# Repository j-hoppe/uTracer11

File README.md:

# uTracer11

„uTracer11“ (read: "micro-program-tracer for PDP-11") is a signal probe that is plugged into older UNIBUS PDP-11s.

The CPU state is visualized on a host PC via a graphical user interface (GUI)

It is primarily used for micro-stepping the CPU, as a function demo, repair tool, or for entertainment.

See: https://www.retrocmp.com/tools/utracer11

## Directory structure:
* common - C++ sources needed for M93X2 Arduino and GUI ... message protocol
* CSerialPort - C++ sources for RS232 interface Linux/Windows
* duktape - embedded JScript engine

* gui - main user interface, WxWidgets project Linux/Windows

* KM11.pcb - KiCad project for KM11 adapter probe

* M93X2probe.pcb - KiCad project for M93X2 probe PCB

* M93X2probe.pio - M93X2 probe Arduino firmware, PlatformI

* M93X2probe.pdp11data - PDP-11 code to be embedded into M93X2 BOOT logic

* Pdp11BusCycleDisas - source branch of UNIBUS traffic disassmebler for different PDP-11 CPUs

* pdp1134sim - case study for a micro machine based simulator, example is a 11/34 simple program loop

* resources - helper data files, scanned jpegs

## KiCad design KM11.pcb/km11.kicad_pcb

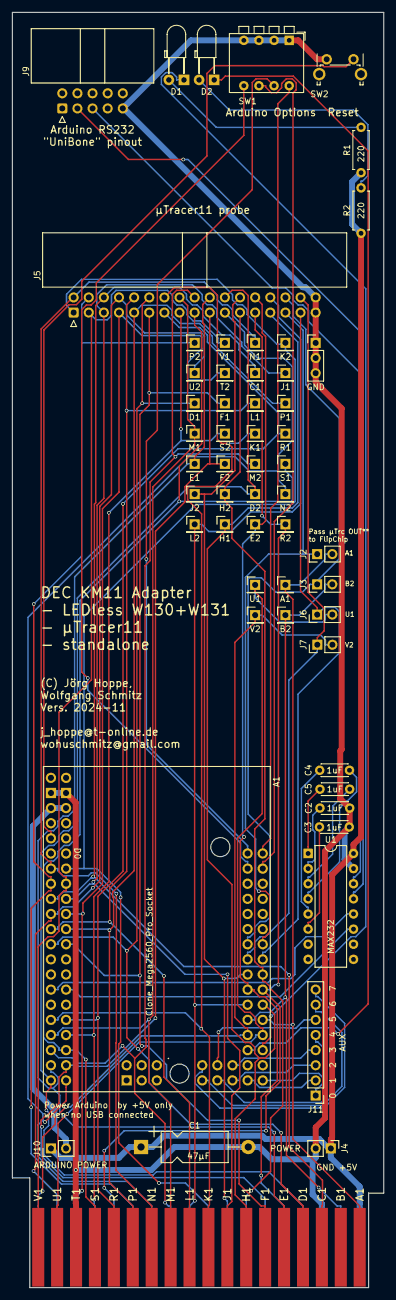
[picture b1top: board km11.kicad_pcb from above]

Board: 2 copper layers, 62.4 x 214.1 mm, 56 parts (0 on the bottom side), 66 nets.

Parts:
A1: Clone_Mega2560_Pro_Socket
C1: 47µF; CP_Axial_L11.0mm_D5.0mm_P18.00mm_Horizontal
C2, C3, C4, C5: 1uF; C_Disc_D4.3mm_W1.9mm_P5.00mm
D1: LED1; LED_D3.0mm_Horizontal_O3.81mm_Z2.0mm
D2: LED2; LED_D3.0mm_Horizontal_O3.81mm_Z2.0mm
J1: PDP11 FlipChipSlot2x18; dec-conn-single-ht-pins-only
J2: PASS_A1; PinHeader_1x02_P2.54mm_Vertical
J3: PASS_B2; PinHeader_1x02_P2.54mm_Vertical
J4: POWER; PinHeader_1x02_P2.54mm_Vertical
J5: µTracer11 2x17 IDC; IDC-Header_2x17_P2.54mm_Horizontal
J6: PASS_U1; PinHeader_1x02_P2.54mm_Vertical
J7: PASS_V2; PinHeader_1x02_P2.54mm_Vertical
J8: GND; PinHeader_1x03_P2.54mm_Vertical
J9: UART1_RS232_Schneid-Klemm_2x5; IDC-Header_2x05_P2.54mm_Horizontal
J10: ARDUINO POWER; PinHeader_1x02_P2.54mm_Vertical
J11: AUX; PinHeader_1x08_P2.54mm_Vertical
R1, R2: 220; R_Axial_DIN0207_L6.3mm_D2.5mm_P7.62mm_Horizontal
SW1: Option; SW_DIP_SPSTx04_Piano_CTS_Series194-4MSTN_W7.62mm_P2.54mm
SW2: Reset; SW_Tactile_SPST_Angled_PTS645Vx58-2LFS
TP1: R2; PinHeader_1x01_P2.54mm_Vertical
TP2: N2; PinHeader_1x01_P2.54mm_Vertical
TP3: S1; PinHeader_1x01_P2.54mm_Vertical
TP4: R1; PinHeader_1x01_P2.54mm_Vertical
TP5: P1; PinHeader_1x01_P2.54mm_Vertical
TP6: J1; PinHeader_1x01_P2.54mm_Vertical
TP7: K2; PinHeader_1x01_P2.54mm_Vertical
TP8: E2; PinHeader_1x01_P2.54mm_Vertical
TP9: D2; PinHeader_1x01_P2.54mm_Vertical
TP10: M2; PinHeader_1x01_P2.54mm_Vertical
TP11: K1; PinHeader_1x01_P2.54mm_Vertical
TP12: L1; PinHeader_1x01_P2.54mm_Vertical
TP13: C1; PinHeader_1x01_P2.54mm_Vertical
TP14: N1; PinHeader_1x01_P2.54mm_Vertical
TP15: H1; PinHeader_1x01_P2.54mm_Vertical
TP16: H2; PinHeader_1x01_P2.54mm_Vertical
TP17: F2; PinHeader_1x01_P2.54mm_Vertical
TP18: S2; PinHeader_1x01_P2.54mm_Vertical
TP19: F1; PinHeader_1x01_P2.54mm_Vertical
TP20: T2; PinHeader_1x01_P2.54mm_Vertical
TP21: V1; PinHeader_1x01_P2.54mm_Vertical
TP22: L2; PinHeader_1x01_P2.54mm_Vertical
TP23: J2; PinHeader_1x01_P2.54mm_Vertical
TP24: E1; PinHeader_1x01_P2.54mm_Vertical
TP25: M1; PinHeader_1x01_P2.54mm_Vertical
TP26: D1; PinHeader_1x01_P2.54mm_Vertical
TP27: U2; PinHeader_1x01_P2.54mm_Vertical
TP28: P2; PinHeader_1x01_P2.54mm_Vertical
TP29: A1; PinHeader_1x01_P2.54mm_Vertical
TP30: B2; PinHeader_1x01_P2.54mm_Vertical
TP31: U1; PinHeader_1x01_P2.54mm_Vertical
TP32: V2; PinHeader_1x01_P2.54mm_Vertical
U1: MAX232; DIP-16_W7.62mm

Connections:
5V: C1.1, J1.A2, J4.1, J10.1, R1.1, R2.1, U1.16 (VCC)
/arduino/ARDUINO_5V: A1.5V1 (5V), A1.5V3 (5V), J10.2
/arduino/AUX0: A1.D46, J11.1
/arduino/AUX1: A1.D47, J11.2
/arduino/AUX2: A1.D48, J11.3
/arduino/AUX3: A1.D49, J11.4
/arduino/AUX4: A1.D50 (D50_MISO), J11.5
/arduino/AUX5: A1.D51 (D51_MOSI), J11.6
/arduino/AUX6: A1.D52 (D52_SCK), J11.7
/arduino/AUX7: A1.D53 (D53_CS), J11.8
/arduino/LED1: A1.D42, D1.1 (K)
/arduino/LED2: A1.D43, D2.1 (K)
/arduino/RS232-RX: A1.D19 (D19/RX1), U1.12 (R1OUT)
/arduino/RS232-TX: A1.D18 (D18/TX1), U1.11 (T1IN)
C1: A1.D7, J1.C1, J5.6, TP13.1
D1: A1.D13, J1.D1, J5.12, TP26.1
D2: A1.D31, J1.D2, J5.22, TP9.1
E1: A1.D29, J1.E1, J5.20, TP24.1
E2: A1.D35, J1.E2, J5.26, TP8.1
F1: A1.D12, J1.F1, J5.11, TP19.1
F2: A1.D28, J1.F2, J5.19, TP17.1
GND: A1.GND1 (GND), A1.GND2 (GND), C1.2, C2.2, C3.2, J1.C2, J1.T1, J4.2, J5.33, J5.34, J8.1, J8.2, J8.3, J9.9 (GND), SW1.1, SW1.2, SW1.3, SW1.4, SW2.1, U1.15 (GND)
H1: A1.D36, J1.H1, J5.27, TP15.1
H2: A1.D32, J1.H2, J5.23, TP16.1
J1: A1.D6, J1.J1, J5.5, TP6.1
J2: A1.D33, J1.J2, J5.24, TP23.1
K1: A1.D23, J1.K1, J5.14, TP11.1
K2: A1.D2 (D2_INT0), J1.K2, J5.1, TP7.1
L1: A1.D11, J1.L1, J5.10, TP12.1
L2: A1.D37, J1.L2, J5.28, TP22.1
M1: A1.D25, J1.M1, J5.16, TP25.1
M2: A1.D27, J1.M2, J5.18, TP10.1
N1: A1.D3 (D3_INT1), J1.N1, J5.2, TP14.1
N2: A1.D30, J1.N2, J5.21, TP2.1
unnamed: A1.A0, SW1.8
unnamed: A1.A1, SW1.7
unnamed: A1.A2, SW1.6
unnamed: A1.A3, SW1.5
unnamed: A1.RST1 (RESET), SW2.2
unnamed: D1.2 (A), R1.2
unnamed: D2.2 (A), R2.2
unnamed: J9.3 (RXD), U1.13 (R1IN)
unnamed: J9.5 (TXD), U1.14 (T1OUT)
unnamed: C5.1, U1.1 (C1+)
unnamed: C5.2, U1.3 (C1-)
unnamed: C4.1, U1.4 (C2+)
unnamed: C4.2, U1.5 (C2-)
unnamed: C2.1, U1.2 (VS+)
unnamed: C3.1, U1.6 (VS-)
P1: A1.D10, J1.P1, J5.9, TP5.1
P2: A1.D5, J1.P2, J5.4, TP28.1
PDP_A1_L: A1.D38, J1.A1, J2.2, TP29.1
PDP_B2_L: A1.D39, J1.B2, J3.2, TP30.1
PDP_U1_L: A1.D40, J1.U1, J6.2, TP31.1
PDP_V2_L: A1.D41, J1.V2, J7.2, TP32.1
R1: A1.D22, J1.R1, J5.13, TP4.1
R2: A1.D34, J1.R2, J5.25, TP1.1
S1: A1.D26, J1.S1, J5.17, TP3.1
S2: A1.D24, J1.S2, J5.15, TP18.1
T2: A1.D8, J1.T2, J5.7, TP20.1
TRACER_A1_L: A1.A12, J2.1, J5.29
TRACER_B2_L: A1.A13, J3.1, J5.30
TRACER_U1_L: A1.A14, J5.31, J6.1
TRACER_V2_L: A1.A15, J5.32, J7.1
U2: A1.D9, J1.U2, J5.8, TP27.1
V1: A1.D4, J1.V1, J5.3, TP21.1

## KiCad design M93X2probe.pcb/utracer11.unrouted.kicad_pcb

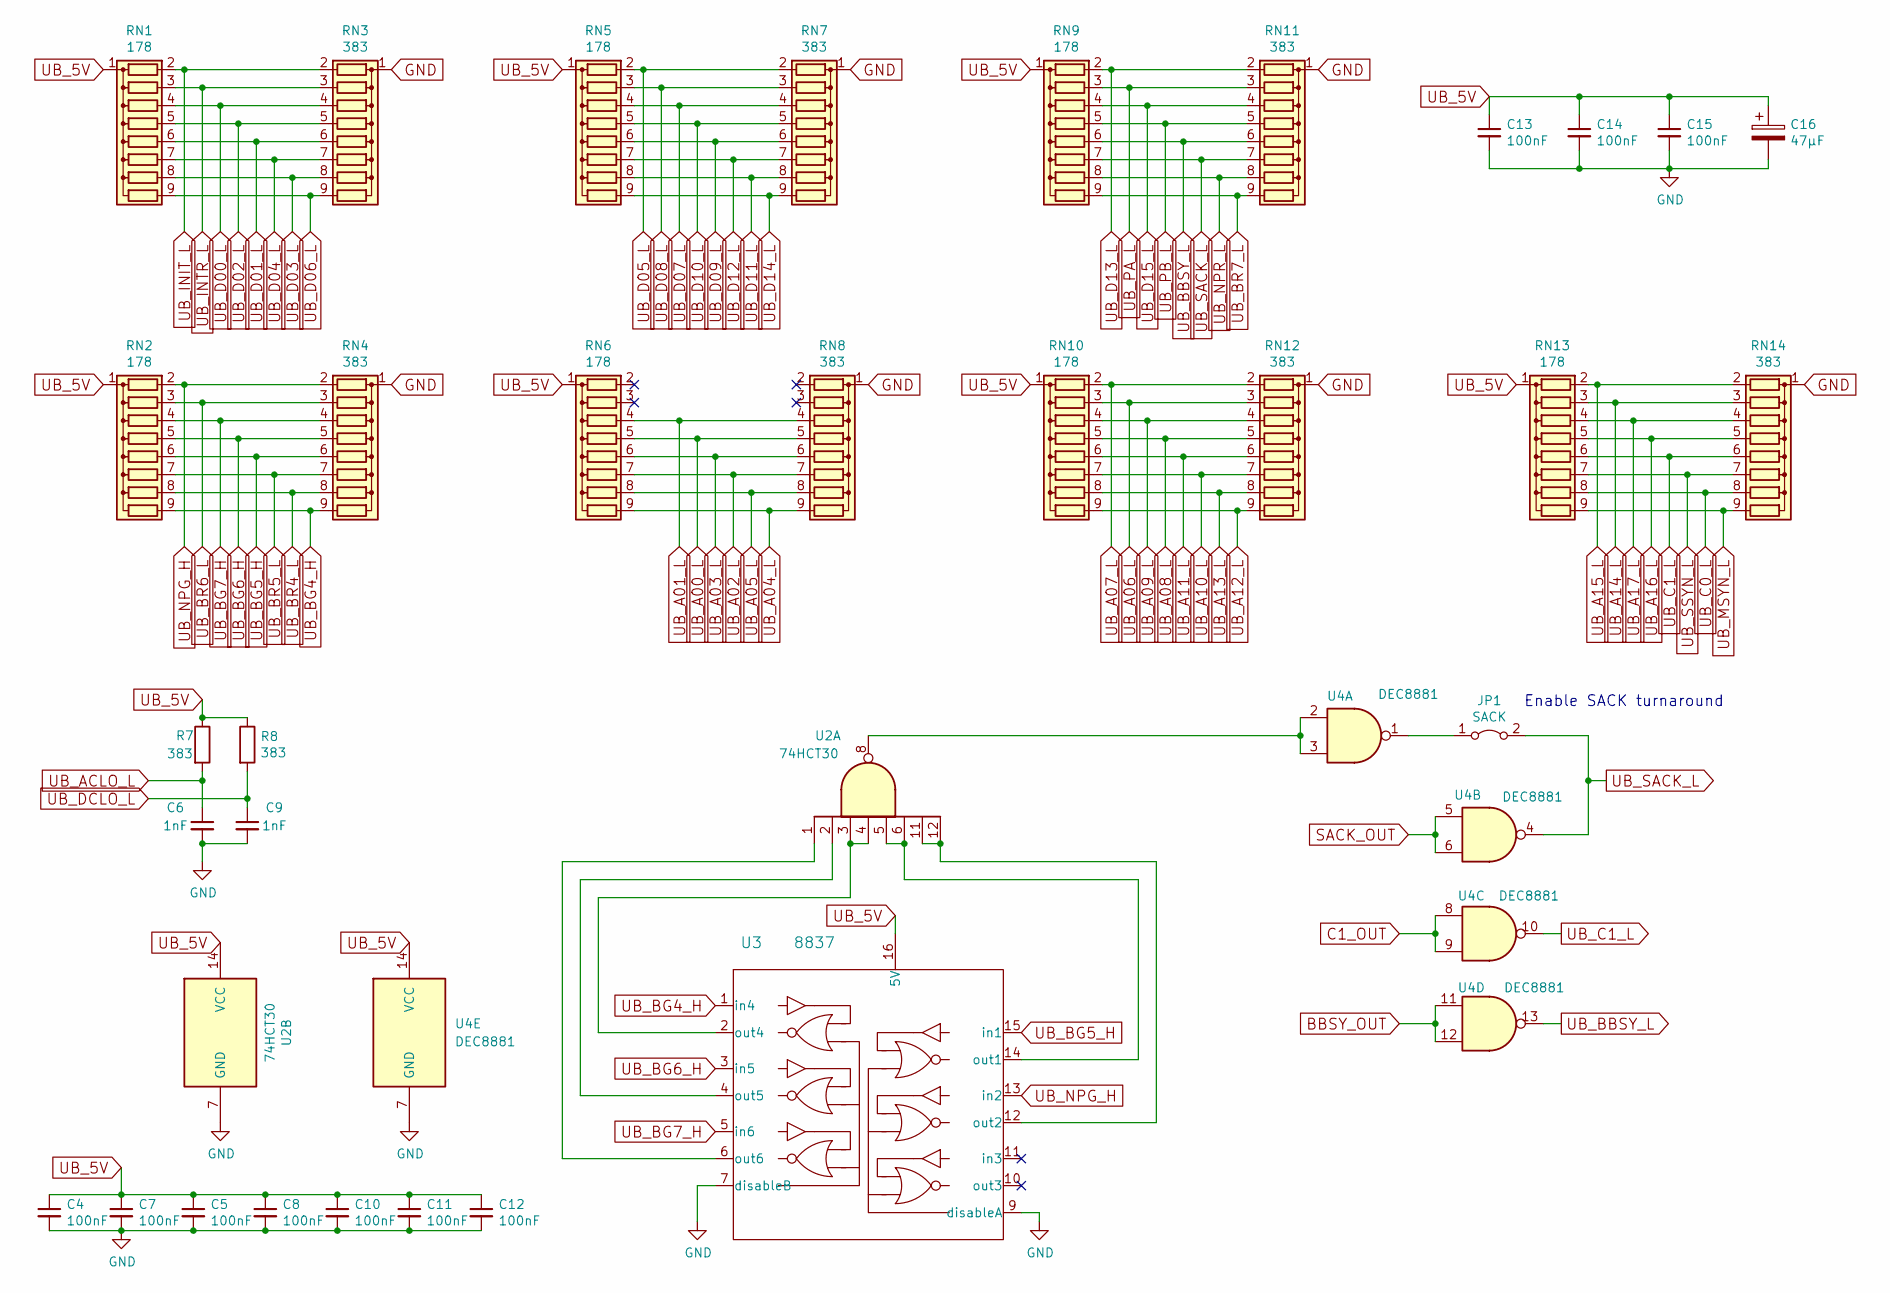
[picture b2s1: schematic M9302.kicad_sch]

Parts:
C4, C5, C7, C8, C10, C11, C12, C13, C14, C15: 100nF; C_Disc_D4.3mm_W1.9mm_P5.00mm; LCSC C49678
C6, C9: 1nF; C_Disc_D4.3mm_W1.9mm_P5.00mm; LCSC C46653
C16: 47µF; CP_Axial_L11.0mm_D5.0mm_P18.00mm_Horizontal
JP1: SACK; PinHeader_1x02_P2.54mm_Vertical
R7, R8: 383; R_Axial_DIN0207_L6.3mm_D2.5mm_P2.54mm_Vertical; LCSC C17655
RN1, RN2, RN5, RN6, RN9, RN10, RN13: 178; R_Array_SIP9
RN3, RN4, RN7, RN8, RN11, RN12, RN14: 383; R_Array_SIP9
U2: 74HCT30; DIP-14_W7.62mm; LCSC C2865549
U3: 8837; DIP-16_W7.62mm
U4: DEC8881; DIP-14_W7.62mm

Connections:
BBSY_OUT: U4.11, U4.12; also elsewhere on the board
C1_OUT: U4.8, U4.9; also elsewhere on the board
GND: C4.2, C5.2, C6.2, C7.2, C8.2, C9.2, C10.2, C11.2, C12.2, C13.2, C14.2, C15.2, C16.2, RN3.1 (common), RN4.1 (common), RN7.1 (common), RN8.1 (common), RN11.1 (common), RN12.1 (common), RN14.1 (common), U2.7 (GND), U3.7 (disableB), U3.8 (GND), U3.9 (disableA), U4.7 (GND); also elsewhere on the board
unnamed: JP1.1 (A), U4.1
unnamed: U2.8, U4.2, U4.3
unnamed: U2.5, U2.6, U3.14 (out1)
unnamed: U2.11, U2.12, U3.12 (out2)
unnamed: U2.3, U2.4, U3.2 (out4)
unnamed: U2.2, U3.4 (out5)
unnamed: U2.1, U3.6 (out6)
SACK_OUT: U4.5, U4.6; also elsewhere on the board
UB_5V: C4.1, C5.1, C7.1, C8.1, C10.1, C11.1, C12.1, C13.1, C14.1, C15.1, C16.1, R7.1, R8.1, RN1.1 (common), RN2.1 (common), RN5.1 (common), RN6.1 (common), RN9.1 (common), RN10.1 (common), RN13.1 (common), U2.14 (VCC), U3.16 (5V), U4.14 (VCC); also elsewhere on the board
UB_A00_L: RN6.5 (R4), RN8.5 (R4); also elsewhere on the board
UB_A01_L: RN6.4 (R3), RN8.4 (R3); also elsewhere on the board
UB_A02_L: RN6.7 (R6), RN8.7 (R6); also elsewhere on the board
UB_A03_L: RN6.6 (R5), RN8.6 (R5); also elsewhere on the board
UB_A04_L: RN6.9 (R8), RN8.9 (R8); also elsewhere on the board
UB_A05_L: RN6.8 (R7), RN8.8 (R7); also elsewhere on the board
UB_A06_L: RN10.3 (R2), RN12.3 (R2); also elsewhere on the board
UB_A07_L: RN10.2 (R1), RN12.2 (R1); also elsewhere on the board
UB_A08_L: RN10.5 (R4), RN12.5 (R4); also elsewhere on the board
UB_A09_L: RN10.4 (R3), RN12.4 (R3); also elsewhere on the board
UB_A10_L: RN10.7 (R6), RN12.7 (R6); also elsewhere on the board
UB_A11_L: RN10.6 (R5), RN12.6 (R5); also elsewhere on the board
UB_A12_L: RN10.9 (R8), RN12.9 (R8); also elsewhere on the board
UB_A13_L: RN10.8 (R7), RN12.8 (R7); also elsewhere on the board
UB_A14_L: RN13.3 (R2), RN14.3 (R2); also elsewhere on the board
UB_A15_L: RN13.2 (R1), RN14.2 (R1); also elsewhere on the board
UB_A16_L: RN13.5 (R4), RN14.5 (R4); also elsewhere on the board
UB_A17_L: RN13.4 (R3), RN14.4 (R3); also elsewhere on the board
UB_ACLO_L: C6.1, R7.2; also elsewhere on the board
UB_BBSY_L: RN9.6 (R5), RN11.6 (R5), U4.13; also elsewhere on the board
UB_BG4_H: RN2.9 (R8), RN4.9 (R8), U3.1 (in4); also elsewhere on the board
UB_BG5_H: RN2.6 (R5), RN4.6 (R5), U3.15 (in1); also elsewhere on the board
UB_BG6_H: RN2.5 (R4), RN4.5 (R4), U3.3 (in5); also elsewhere on the board
UB_BG7_H: RN2.4 (R3), RN4.4 (R3), U3.5 (in6); also elsewhere on the board
UB_BR4_L: RN2.8 (R7), RN4.8 (R7); also elsewhere on the board
UB_BR5_L: RN2.7 (R6), RN4.7 (R6); also elsewhere on the board
UB_BR6_L: RN2.3 (R2), RN4.3 (R2); also elsewhere on the board
UB_BR7_L: RN9.9 (R8), RN11.9 (R8); also elsewhere on the board
UB_C0_L: RN13.8 (R7), RN14.8 (R7); also elsewhere on the board
UB_C1_L: RN13.6 (R5), RN14.6 (R5), U4.10; also elsewhere on the board
UB_D00_L: RN1.4 (R3), RN3.4 (R3); also elsewhere on the board
UB_D01_L: RN1.6 (R5), RN3.6 (R5); also elsewhere on the board
UB_D02_L: RN1.5 (R4), RN3.5 (R4); also elsewhere on the board
UB_D03_L: RN1.8 (R7), RN3.8 (R7); also elsewhere on the board
UB_D04_L: RN1.7 (R6), RN3.7 (R6); also elsewhere on the board
UB_D05_L: RN5.2 (R1), RN7.2 (R1); also elsewhere on the board
UB_D06_L: RN1.9 (R8), RN3.9 (R8); also elsewhere on the board
UB_D07_L: RN5.4 (R3), RN7.4 (R3); also elsewhere on the board
UB_D08_L: RN5.3 (R2), RN7.3 (R2); also elsewhere on the board
UB_D09_L: RN5.6 (R5), RN7.6 (R5); also elsewhere on the board
UB_D10_L: RN5.5 (R4), RN7.5 (R4); also elsewhere on the board
UB_D11_L: RN5.8 (R7), RN7.8 (R7); also elsewhere on the board
UB_D12_L: RN5.7 (R6), RN7.7 (R6); also elsewhere on the board
UB_D13_L: RN9.2 (R1), RN11.2 (R1); also elsewhere on the board
UB_D14_L: RN5.9 (R8), RN7.9 (R8); also elsewhere on the board
UB_D15_L: RN9.4 (R3), RN11.4 (R3); also elsewhere on the board
UB_DCLO_L: C9.1, R8.2; also elsewhere on the board
UB_INIT_L: RN1.2 (R1), RN3.2 (R1); also elsewhere on the board
UB_INTR_L: RN1.3 (R2), RN3.3 (R2); also elsewhere on the board
UB_MSYN_L: RN13.9 (R8), RN14.9 (R8); also elsewhere on the board
UB_NPG_H: RN2.2 (R1), RN4.2 (R1), U3.13 (in2); also elsewhere on the board
UB_NPR_L: RN9.8 (R7), RN11.8 (R7); also elsewhere on the board
UB_PA_L: RN9.3 (R2), RN11.3 (R2); also elsewhere on the board
UB_PB_L: RN9.5 (R4), RN11.5 (R4); also elsewhere on the board
UB_SACK_L: JP1.2 (B), RN9.7 (R6), RN11.7 (R6), U4.4; also elsewhere on the board
UB_SSYN_L: RN13.7 (R6), RN14.7 (R6); also elsewhere on the board

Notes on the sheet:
Enable SACK turnaround

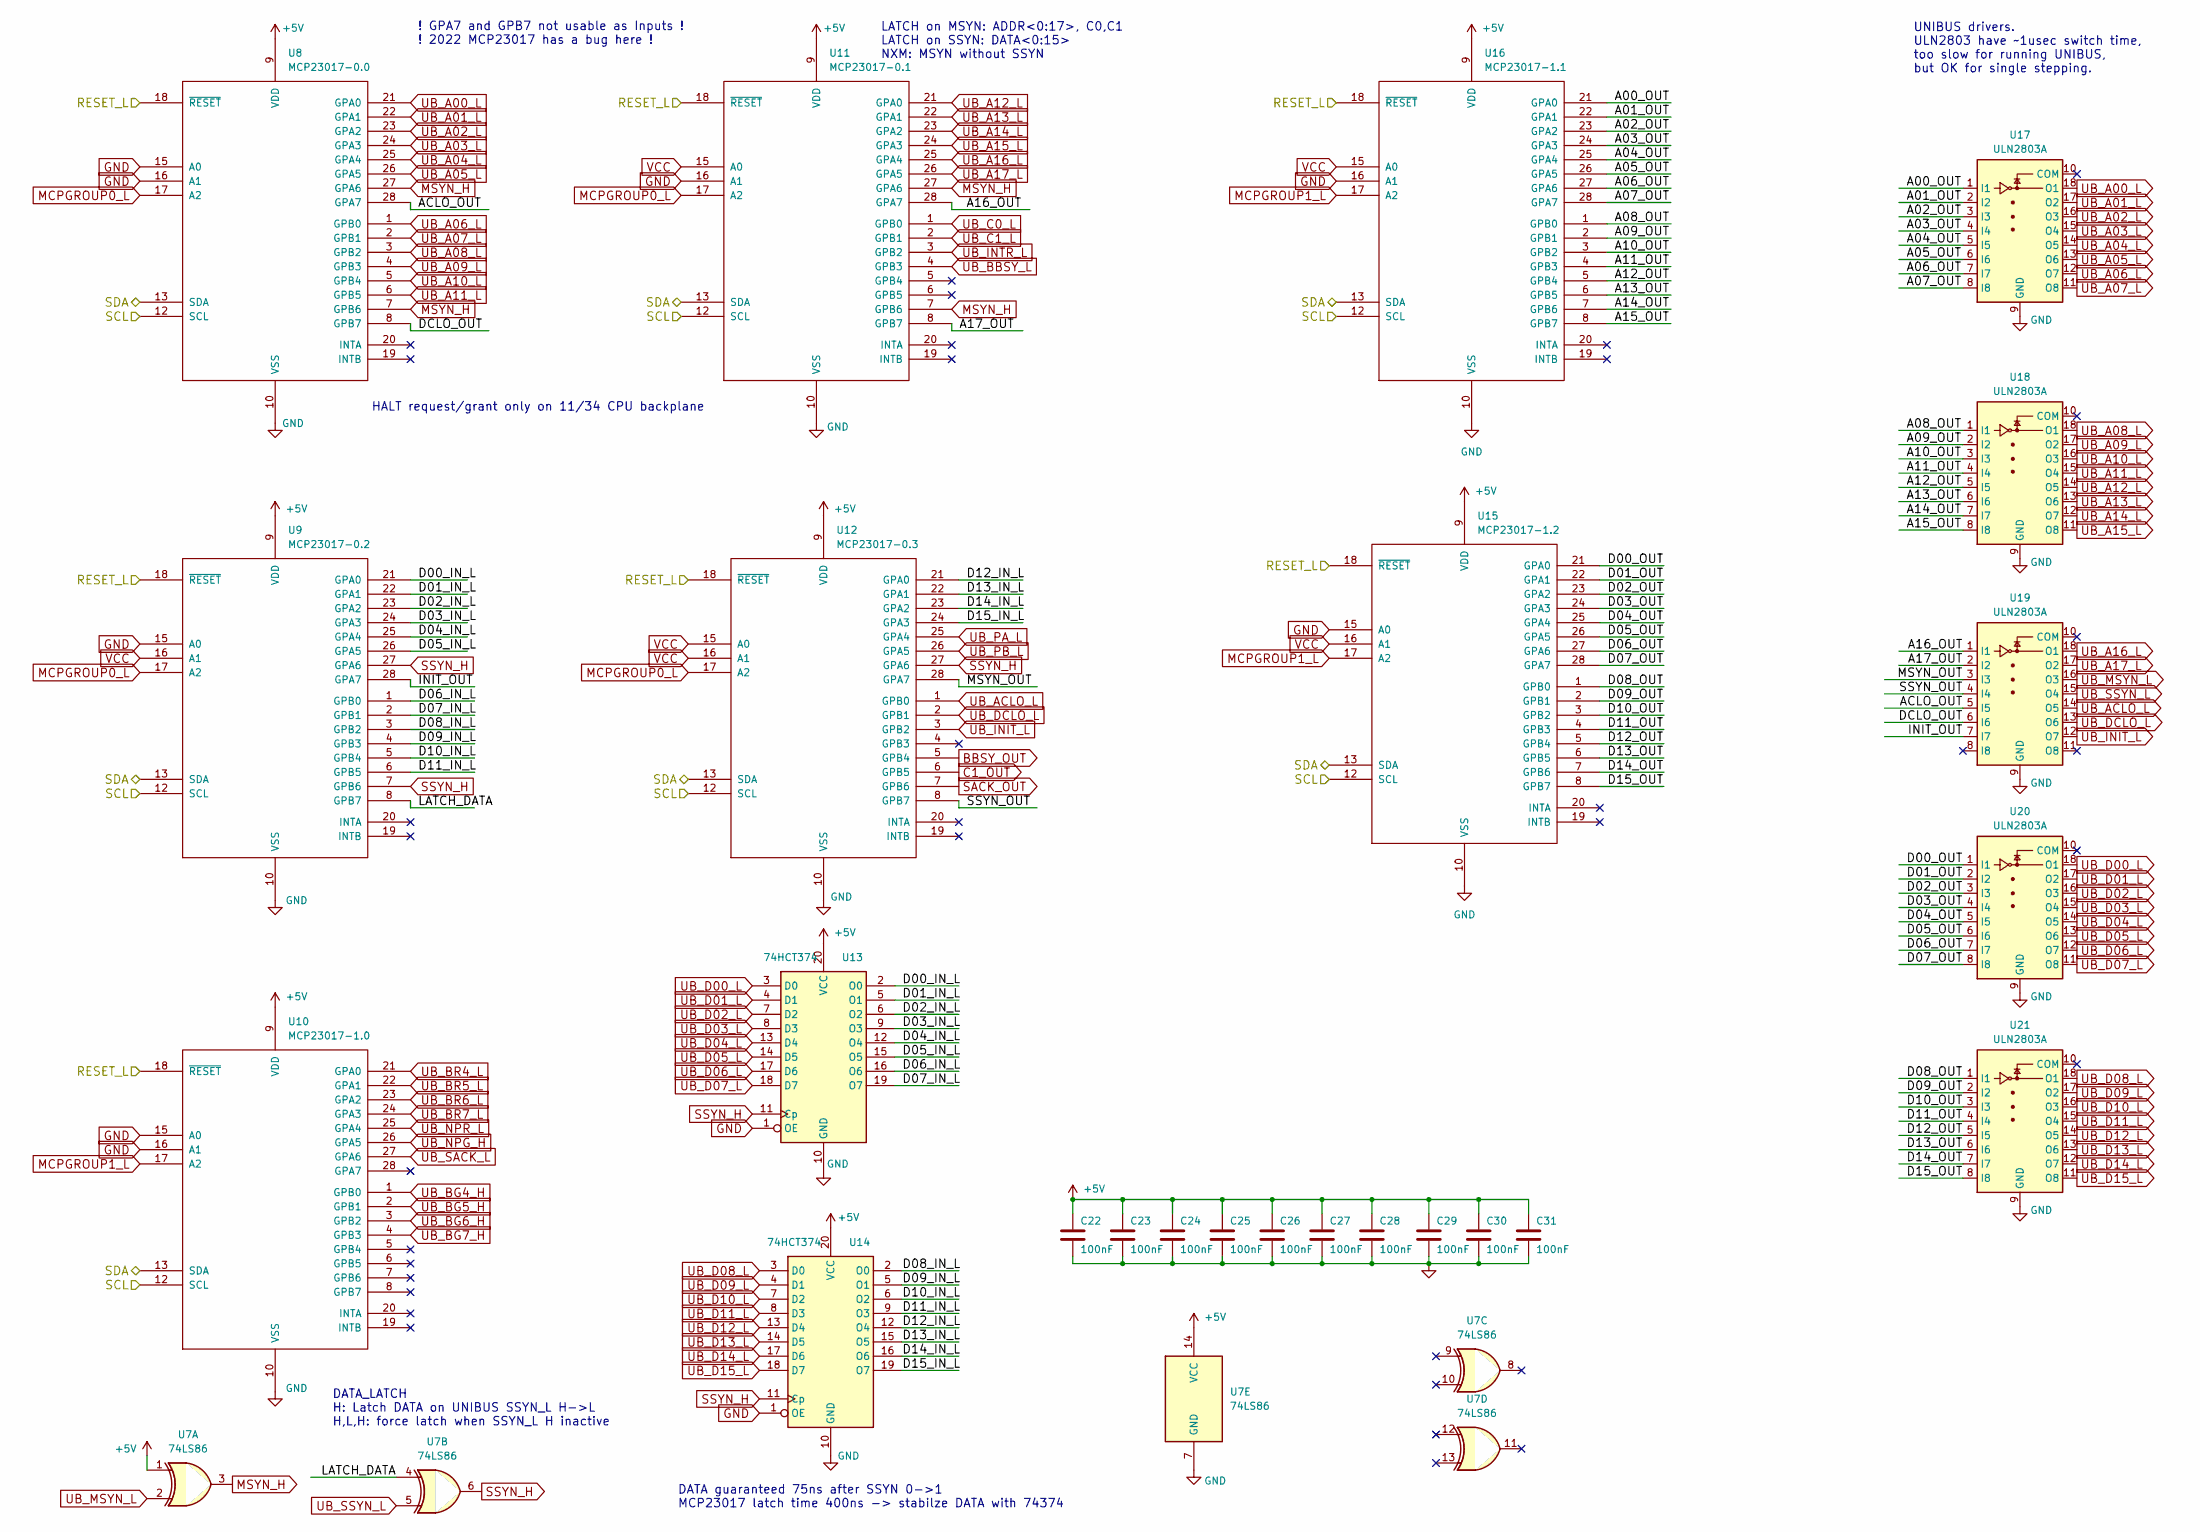
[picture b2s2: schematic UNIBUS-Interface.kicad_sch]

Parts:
C22, C23, C24, C25, C26, C27, C28, C29, C30, C31: 100nF; C_Disc_D4.3mm_W1.9mm_P5.00mm
U7: 74LS86; DIP-14_W7.62mm
U8: MCP23017-0.0; DIP-28_W7.62mm
U9: MCP23017-0.2; DIP-28_W7.62mm
U10: MCP23017-1.0; DIP-28_W7.62mm
U11: MCP23017-0.1; DIP-28_W7.62mm
U12: MCP23017-0.3; DIP-28_W7.62mm
U13, U14: 74HCT374; DIP-20_W7.62mm
U15: MCP23017-1.2; DIP-28_W7.62mm
U16: MCP23017-1.1; DIP-28_W7.62mm
U17, U18, U19, U20, U21: ULN2803A; DIP-18_W7.62mm

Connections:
/MCP_RESET_L: U8.18 (~RESET), U9.18 (~RESET), U10.18 (~RESET), U11.18 (~RESET), U12.18 (~RESET), U15.18 (~RESET), U16.18 (~RESET); also elsewhere on the board
/SCL: U8.12 (SCL), U9.12 (SCL), U10.12 (SCL), U11.12 (SCL), U12.12 (SCL), U15.12 (SCL), U16.12 (SCL); also elsewhere on the board
/SDA: U8.13 (SDA), U9.13 (SDA), U10.13 (SDA), U11.13 (SDA), U12.13 (SDA), U15.13 (SDA), U16.13 (SDA); also elsewhere on the board
/UNIBUS-Interface/A00_OUT: U16.21 (GPA0), U17.1 (I1)
/UNIBUS-Interface/A01_OUT: U16.22 (GPA1), U17.2 (I2)
/UNIBUS-Interface/A02_OUT: U16.23 (GPA2), U17.3 (I3)
/UNIBUS-Interface/A03_OUT: U16.24 (GPA3), U17.4 (I4)
/UNIBUS-Interface/A04_OUT: U16.25 (GPA4), U17.5 (I5)
/UNIBUS-Interface/A05_OUT: U16.26 (GPA5), U17.6 (I6)
/UNIBUS-Interface/A06_OUT: U16.27 (GPA6), U17.7 (I7)
/UNIBUS-Interface/A07_OUT: U16.28 (GPA7), U17.8 (I8)
/UNIBUS-Interface/A08_OUT: U16.1 (GPB0), U18.1 (I1)
/UNIBUS-Interface/A09_OUT: U16.2 (GPB1), U18.2 (I2)
/UNIBUS-Interface/A10_OUT: U16.3 (GPB2), U18.3 (I3)
/UNIBUS-Interface/A11_OUT: U16.4 (GPB3), U18.4 (I4)
/UNIBUS-Interface/A12_OUT: U16.5 (GPB4), U18.5 (I5)
/UNIBUS-Interface/A13_OUT: U16.6 (GPB5), U18.6 (I6)
/UNIBUS-Interface/A14_OUT: U16.7 (GPB6), U18.7 (I7)
/UNIBUS-Interface/A15_OUT: U16.8 (GPB7), U18.8 (I8)
/UNIBUS-Interface/A16_OUT: U11.28 (GPA7), U19.1 (I1)
/UNIBUS-Interface/A17_OUT: U11.8 (GPB7), U19.2 (I2)
/UNIBUS-Interface/ACLO_OUT: U8.28 (GPA7), U19.5 (I5)
/UNIBUS-Interface/D00_IN_L: U9.21 (GPA0), U13.2 (O0)
/UNIBUS-Interface/D00_OUT: U15.21 (GPA0), U20.1 (I1)
/UNIBUS-Interface/D01_IN_L: U9.22 (GPA1), U13.5 (O1)
/UNIBUS-Interface/D01_OUT: U15.22 (GPA1), U20.2 (I2)
/UNIBUS-Interface/D02_IN_L: U9.23 (GPA2), U13.6 (O2)
/UNIBUS-Interface/D02_OUT: U15.23 (GPA2), U20.3 (I3)
/UNIBUS-Interface/D03_IN_L: U9.24 (GPA3), U13.9 (O3)
/UNIBUS-Interface/D03_OUT: U15.24 (GPA3), U20.4 (I4)
/UNIBUS-Interface/D04_IN_L: U9.25 (GPA4), U13.12 (O4)
/UNIBUS-Interface/D04_OUT: U15.25 (GPA4), U20.5 (I5)
/UNIBUS-Interface/D05_IN_L: U9.26 (GPA5), U13.15 (O5)
/UNIBUS-Interface/D05_OUT: U15.26 (GPA5), U20.6 (I6)
/UNIBUS-Interface/D06_IN_L: U9.1 (GPB0), U13.16 (O6)
/UNIBUS-Interface/D06_OUT: U15.27 (GPA6), U20.7 (I7)
/UNIBUS-Interface/D07_IN_L: U9.2 (GPB1), U13.19 (O7)
/UNIBUS-Interface/D07_OUT: U15.28 (GPA7), U20.8 (I8)
/UNIBUS-Interface/D08_IN_L: U9.3 (GPB2), U14.2 (O0)
/UNIBUS-Interface/D08_OUT: U15.1 (GPB0), U21.1 (I1)
/UNIBUS-Interface/D09_IN_L: U9.4 (GPB3), U14.5 (O1)
/UNIBUS-Interface/D09_OUT: U15.2 (GPB1), U21.2 (I2)
/UNIBUS-Interface/D10_IN_L: U9.5 (GPB4), U14.6 (O2)
/UNIBUS-Interface/D10_OUT: U15.3 (GPB2), U21.3 (I3)
/UNIBUS-Interface/D11_IN_L: U9.6 (GPB5), U14.9 (O3)
/UNIBUS-Interface/D11_OUT: U15.4 (GPB3), U21.4 (I4)
/UNIBUS-Interface/D12_IN_L: U12.21 (GPA0), U14.12 (O4)
/UNIBUS-Interface/D12_OUT: U15.5 (GPB4), U21.5 (I5)
/UNIBUS-Interface/D13_IN_L: U12.22 (GPA1), U14.15 (O5)
/UNIBUS-Interface/D13_OUT: U15.6 (GPB5), U21.6 (I6)
/UNIBUS-Interface/D14_IN_L: U12.23 (GPA2), U14.16 (O6)
/UNIBUS-Interface/D14_OUT: U15.7 (GPB6), U21.7 (I7)
/UNIBUS-Interface/D15_IN_L: U12.24 (GPA3), U14.19 (O7)
/UNIBUS-Interface/D15_OUT: U15.8 (GPB7), U21.8 (I8)
/UNIBUS-Interface/DCLO_OUT: U8.8 (GPB7), U19.6 (I6)
/UNIBUS-Interface/INIT_OUT: U9.28 (GPA7), U19.7 (I7)
/UNIBUS-Interface/LATCH_DATA: U7.4, U9.8 (GPB7)
/UNIBUS-Interface/MSYN_OUT: U12.28 (GPA7), U19.3 (I3)
/UNIBUS-Interface/SSYN_OUT: U12.8 (GPB7), U19.4 (I4)
BBSY_OUT: U12.5 (GPB4); also elsewhere on the board
C1_OUT: U12.6 (GPB5); also elsewhere on the board
GND: C22.2, C23.2, C24.2, C25.2, C26.2, C27.2, C28.2, C29.2, C30.2, C31.2, U7.7 (GND), U8.10 (VSS), U8.15 (A0), U8.16 (A1), U9.10 (VSS), U9.15 (A0), U10.10 (VSS), U10.15 (A0), U10.16 (A1), U11.10 (VSS), U11.16 (A1), U12.10 (VSS), U13.1 (OE), U13.10 (GND), U14.1 (OE), U14.10 (GND), U15.10 (VSS), U15.15 (A0), U16.10 (VSS), U16.16 (A1), U17.9 (GND), U18.9 (GND), U19.9 (GND), U20.9 (GND), U21.9 (GND); also elsewhere on the board
MCPGROUP0_L: U8.17 (A2), U9.17 (A2), U11.17 (A2), U12.17 (A2); also elsewhere on the board
MCPGROUP1_L: U10.17 (A2), U15.17 (A2), U16.17 (A2); also elsewhere on the board
MSYN_H: U7.3, U8.7 (GPB6), U8.27 (GPA6), U11.7 (GPB6), U11.27 (GPA6)
SACK_OUT: U12.7 (GPB6); also elsewhere on the board
SSYN_H: U7.6, U9.7 (GPB6), U9.27 (GPA6), U12.27 (GPA6), U13.11 (Cp), U14.11 (Cp)
UB_5V: C22.1, C23.1, C24.1, C25.1, C26.1, C27.1, C28.1, C29.1, C30.1, C31.1, U7.1, U7.14 (VCC), U8.9 (VDD), U9.9 (VDD), U9.16 (A1), U10.9 (VDD), U11.9 (VDD), U11.15 (A0), U12.9 (VDD), U12.15 (A0), U12.16 (A1), U13.20 (VCC), U14.20 (VCC), U15.9 (VDD), U15.16 (A1), U16.9 (VDD), U16.15 (A0); also elsewhere on the board
UB_A00_L: U8.21 (GPA0), U17.18 (O1); also elsewhere on the board
UB_A01_L: U8.22 (GPA1), U17.17 (O2); also elsewhere on the board
UB_A02_L: U8.23 (GPA2), U17.16 (O3); also elsewhere on the board
UB_A03_L: U8.24 (GPA3), U17.15 (O4); also elsewhere on the board
UB_A04_L: U8.25 (GPA4), U17.14 (O5); also elsewhere on the board
UB_A05_L: U8.26 (GPA5), U17.13 (O6); also elsewhere on the board
UB_A06_L: U8.1 (GPB0), U17.12 (O7); also elsewhere on the board
UB_A07_L: U8.2 (GPB1), U17.11 (O8); also elsewhere on the board
UB_A08_L: U8.3 (GPB2), U18.18 (O1); also elsewhere on the board
UB_A09_L: U8.4 (GPB3), U18.17 (O2); also elsewhere on the board
UB_A10_L: U8.5 (GPB4), U18.16 (O3); also elsewhere on the board
UB_A11_L: U8.6 (GPB5), U18.15 (O4); also elsewhere on the board
UB_A12_L: U11.21 (GPA0), U18.14 (O5); also elsewhere on the board
UB_A13_L: U11.22 (GPA1), U18.13 (O6); also elsewhere on the board
UB_A14_L: U11.23 (GPA2), U18.12 (O7); also elsewhere on the board
UB_A15_L: U11.24 (GPA3), U18.11 (O8); also elsewhere on the board
UB_A16_L: U11.25 (GPA4), U19.18 (O1); also elsewhere on the board
UB_A17_L: U11.26 (GPA5), U19.17 (O2); also elsewhere on the board
UB_ACLO_L: U12.1 (GPB0), U19.14 (O5); also elsewhere on the board
UB_BBSY_L: U11.4 (GPB3); also elsewhere on the board
UB_BG4_H: U10.1 (GPB0); also elsewhere on the board
UB_BG5_H: U10.2 (GPB1); also elsewhere on the board
UB_BG6_H: U10.3 (GPB2); also elsewhere on the board
UB_BG7_H: U10.4 (GPB3); also elsewhere on the board
UB_BR4_L: U10.21 (GPA0); also elsewhere on the board
UB_BR5_L: U10.22 (GPA1); also elsewhere on the board
UB_BR6_L: U10.23 (GPA2); also elsewhere on the board
UB_BR7_L: U10.24 (GPA3); also elsewhere on the board
UB_C0_L: U11.1 (GPB0); also elsewhere on the board
UB_C1_L: U11.2 (GPB1); also elsewhere on the board
UB_D00_L: U13.3 (D0), U20.18 (O1); also elsewhere on the board
UB_D01_L: U13.4 (D1), U20.17 (O2); also elsewhere on the board
UB_D02_L: U13.7 (D2), U20.16 (O3); also elsewhere on the board
UB_D03_L: U13.8 (D3), U20.15 (O4); also elsewhere on the board
UB_D04_L: U13.13 (D4), U20.14 (O5); also elsewhere on the board
UB_D05_L: U13.14 (D5), U20.13 (O6); also elsewhere on the board
UB_D06_L: U13.17 (D6), U20.12 (O7); also elsewhere on the board
UB_D07_L: U13.18 (D7), U20.11 (O8); also elsewhere on the board
UB_D08_L: U14.3 (D0), U21.18 (O1); also elsewhere on the board
UB_D09_L: U14.4 (D1), U21.17 (O2); also elsewhere on the board
UB_D10_L: U14.7 (D2), U21.16 (O3); also elsewhere on the board
UB_D11_L: U14.8 (D3), U21.15 (O4); also elsewhere on the board
UB_D12_L: U14.13 (D4), U21.14 (O5); also elsewhere on the board
UB_D13_L: U14.14 (D5), U21.13 (O6); also elsewhere on the board
UB_D14_L: U14.17 (D6), U21.12 (O7); also elsewhere on the board
UB_D15_L: U14.18 (D7), U21.11 (O8); also elsewhere on the board
UB_DCLO_L: U12.2 (GPB1), U19.13 (O6); also elsewhere on the board
UB_INIT_L: U12.3 (GPB2), U19.12 (O7); also elsewhere on the board
UB_INTR_L: U11.3 (GPB2); also elsewhere on the board
UB_MSYN_L: U7.2, U19.16 (O3); also elsewhere on the board
UB_NPG_H: U10.26 (GPA5); also elsewhere on the board
UB_NPR_L: U10.25 (GPA4); also elsewhere on the board
UB_PA_L: U12.25 (GPA4); also elsewhere on the board
UB_PB_L: U12.26 (GPA5); also elsewhere on the board
UB_SACK_L: U10.27 (GPA6); also elsewhere on the board
UB_SSYN_L: U7.5, U19.15 (O4); also elsewhere on the board

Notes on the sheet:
! GPA7 and GPB7 not usable as Inputs ! ! 2022 MCP23017 has a bug here !
LATCH on MSYN: ADDR<0:17>, C0,C1 LATCH on SSYN: DATA<0:15> NXM: MSYN without SSYN
HALT request/grant only on 11/34 CPU backplane
UNIBUS drivers. ULN2803 have ~1usec switch time, too slow for running UNIBUS, but OK for single stepping.
DATA guaranteed 75ns after SSYN 0->1 MCP23017 latch time 400ns -> stabilze DATA with 74374
DATA_LATCH H: Latch DATA on UNIBUS SSYN_L H->L H,L,H: force latch when SSYN_L H inactive

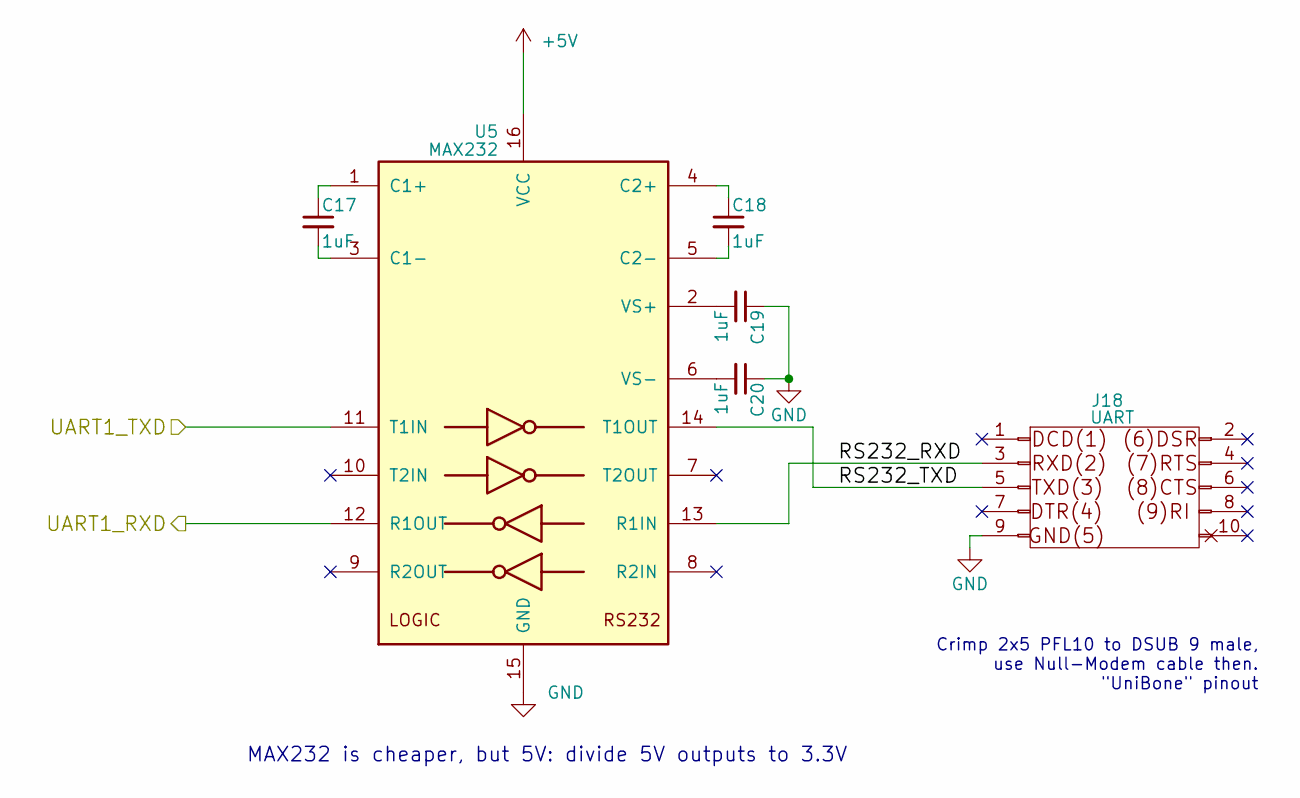
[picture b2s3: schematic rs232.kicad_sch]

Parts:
C17, C19, C20: 1uF; C_Disc_D4.3mm_W1.9mm_P5.00mm; LCSC C28323
C18: 1uF; C_Disc_D4.3mm_W1.9mm_P5.00mm
J18: UART; IDC-Header_2x05_P2.54mm_Horizontal
U5: MAX232; DIP-16_W7.62mm

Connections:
/RS232_RXD: U5.12 (R1OUT); also elsewhere on the board
/RS232_TXD: U5.11 (T1IN); also elsewhere on the board
/rs232/RS232_RXD: J18.3 (RXD), U5.13 (R1IN)
/rs232/RS232_TXD: J18.5 (TXD), U5.14 (T1OUT)
GND: C19.1, C20.1, J18.9 (GND), U5.15 (GND); also elsewhere on the board
unnamed: C17.1, U5.1 (C1+)
unnamed: C17.2, U5.3 (C1-)
unnamed: C18.1, U5.4 (C2+)
unnamed: C18.2, U5.5 (C2-)
unnamed: C19.2, U5.2 (VS+)
unnamed: C20.2, U5.6 (VS-)
UB_5V: U5.16 (VCC); also elsewhere on the board

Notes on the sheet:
MAX232 is cheaper, but 5V: divide 5V outputs to 3.3V
Crimp 2x5 PFL10 to DSUB 9 male, use Null-Modem cable then. "UniBone" pinout

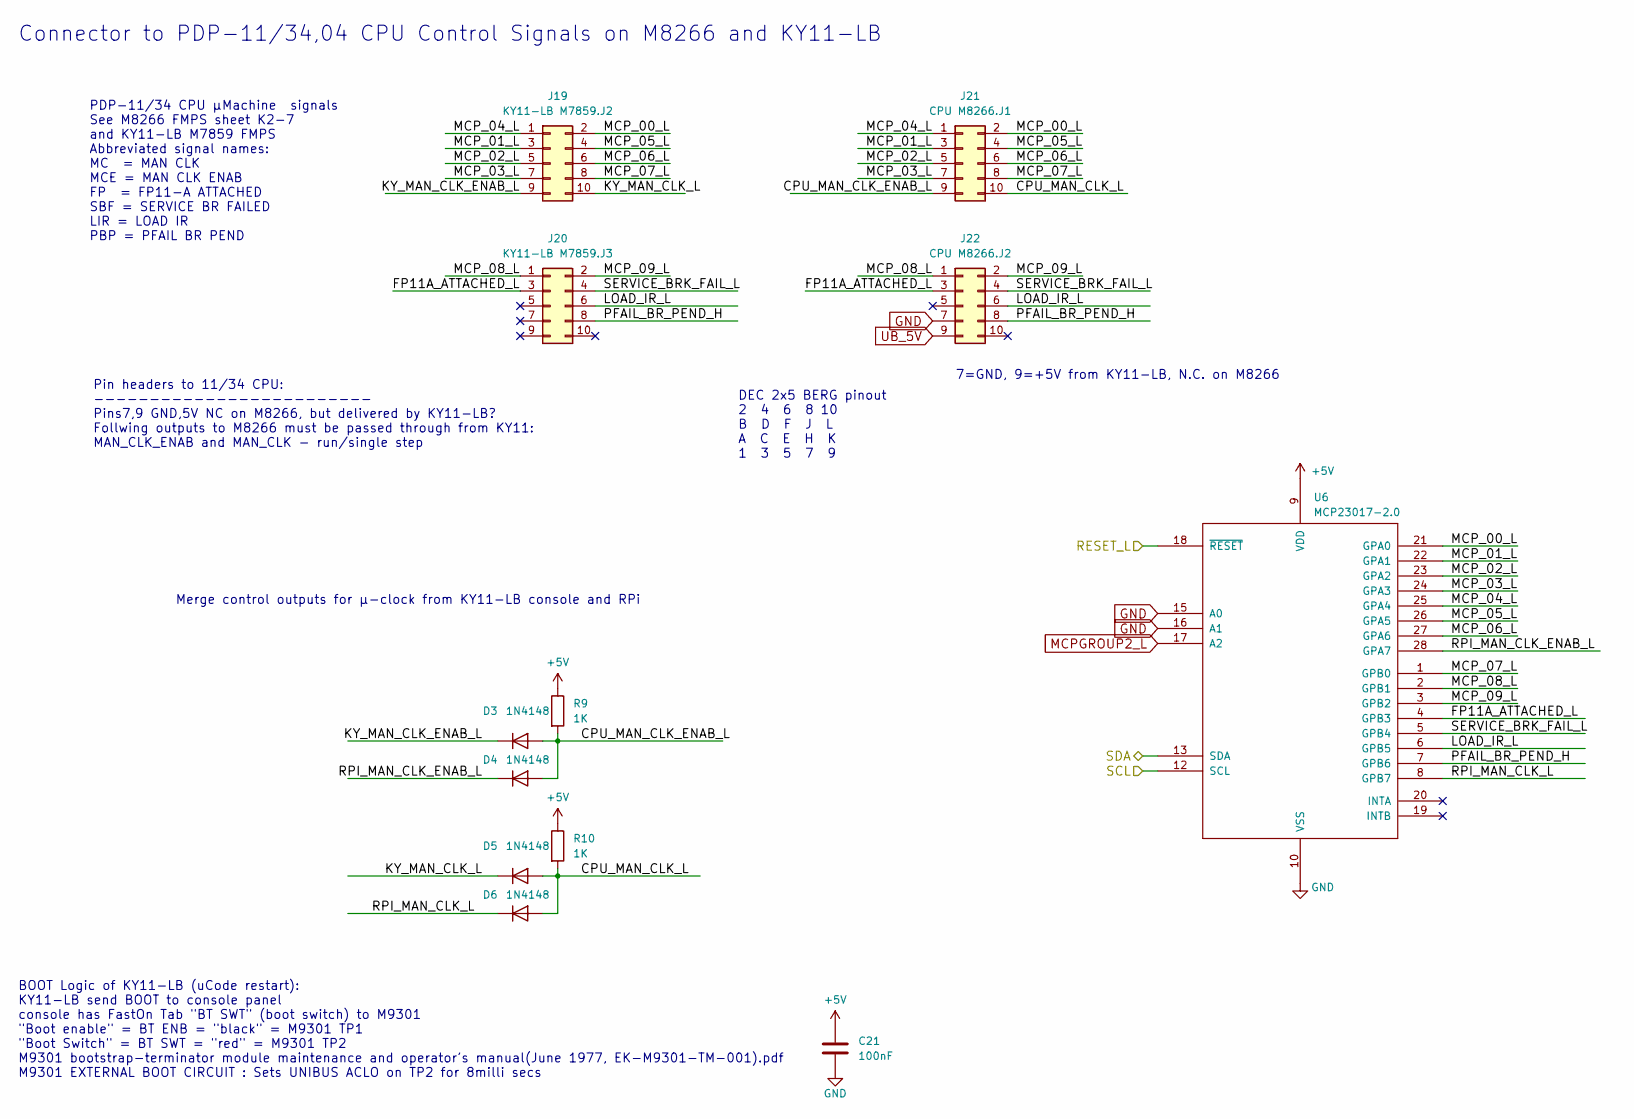
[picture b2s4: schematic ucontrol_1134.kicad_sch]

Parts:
C21: 100nF; C_Disc_D4.3mm_W1.9mm_P5.00mm
D3, D4, D5, D6: 1N4148; D_DO-35_SOD27_P2.54mm_Vertical_AnodeUp
J19: KY11-LB M7859.J2; IDC-Header_2x05_P2.54mm_Horizontal
J20: KY11-LB M7859.J3; IDC-Header_2x05_P2.54mm_Horizontal
J21: CPU M8266.J1; IDC-Header_2x05_P2.54mm_Horizontal
J22: CPU M8266.J2; IDC-Header_2x05_P2.54mm_Horizontal
R9, R10: 1K; R_Axial_DIN0207_L6.3mm_D2.5mm_P2.54mm_Vertical
U6: MCP23017-2.0; DIP-28_W7.62mm

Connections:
/MCP_RESET_L: U6.18 (~RESET); also elsewhere on the board
/SCL: U6.12 (SCL); also elsewhere on the board
/SDA: U6.13 (SDA); also elsewhere on the board
/ucontrol_1134/CPU_MAN_CLK_ENAB_L: D3.2 (A), D4.2 (A), J21.9, R9.2
/ucontrol_1134/CPU_MAN_CLK_L: D5.2 (A), D6.2 (A), J21.10, R10.2
/ucontrol_1134/FP11A_ATTACHED_L: J20.3, J22.3, U6.4 (GPB3)
/ucontrol_1134/KY_MAN_CLK_ENAB_L: D3.1 (K), J19.9
/ucontrol_1134/KY_MAN_CLK_L: D5.1 (K), J19.10
/ucontrol_1134/LOAD_IR_L: J20.6, J22.6, U6.6 (GPB5)
/ucontrol_1134/MCP_00_L: J19.2, J21.2, U6.21 (GPA0)
/ucontrol_1134/MCP_01_L: J19.3, J21.3, U6.22 (GPA1)
/ucontrol_1134/MCP_02_L: J19.5, J21.5, U6.23 (GPA2)
/ucontrol_1134/MCP_03_L: J19.7, J21.7, U6.24 (GPA3)
/ucontrol_1134/MCP_04_L: J19.1, J21.1, U6.25 (GPA4)
/ucontrol_1134/MCP_05_L: J19.4, J21.4, U6.26 (GPA5)
/ucontrol_1134/MCP_06_L: J19.6, J21.6, U6.27 (GPA6)
/ucontrol_1134/MCP_07_L: J19.8, J21.8, U6.1 (GPB0)
/ucontrol_1134/MCP_08_L: J20.1, J22.1, U6.2 (GPB1)
/ucontrol_1134/MCP_09_L: J20.2, J22.2, U6.3 (GPB2)
/ucontrol_1134/PFAIL_BR_PEND_H: J20.8, J22.8, U6.7 (GPB6)
/ucontrol_1134/RPI_MAN_CLK_ENAB_L: D4.1 (K), U6.28 (GPA7)
/ucontrol_1134/RPI_MAN_CLK_L: D6.1 (K), U6.8 (GPB7)
/ucontrol_1134/SERVICE_BRK_FAIL_L: J20.4, J22.4, U6.5 (GPB4)
GND: C21.2, J22.7, U6.10 (VSS), U6.15 (A0), U6.16 (A1); also elsewhere on the board
MCPGROUP2_L: U6.17 (A2); also elsewhere on the board
UB_5V: C21.1, J22.9, R9.1, R10.1, U6.9 (VDD); also elsewhere on the board

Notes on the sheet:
Merge control outputs for µ-clock from KY11-LB console and RPi
Pin headers to 11/34 CPU: ------------------------- Pins7,9 GND,5V NC on M8266, but delivered by KY11-LB? Follwing outputs to M8266 must be passed through from KY11: MAN_CLK_ENAB and MAN_CLK - run/single step
Connector to PDP-11/34,04 CPU Control Signals on M8266 and KY11-LB
DEC 2x5 BERG pinout 2 4 6 8 10 B D F J L A C E H K 1 3 5 7 9
BOOT Logic of KY11-LB (uCode restart): KY11-LB send BOOT to console panel console has FastOn Tab "BT SWT" (boot switch) to M9301 "Boot enable" = BT ENB = "black" = M9301 TP1 "Boot Switch" = BT SWT = "red" = M9301 TP2 M9301 bootstrap-terminator module maintenance and operator's manual(June 1977, EK-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
PDP-11/34 CPU µMachine signals See M8266 FMPS sheet K2-7 and KY11-LB M7859 FMPS Abbreviated signal names: MC = MAN CLK MCE = MAN CLK ENAB FP = FP11-A ATTACHED SBF = SERVICE BR FAILED LIR = LOAD IR PBP = PFAIL BR PEND
7=GND, 9=+5V from KY11-LB, N.C. on M8266
